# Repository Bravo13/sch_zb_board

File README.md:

# Schneider Sedna Wallswitch ZigBee board
To make regular switch ZigBee-powered and keep it compact

## Hardware
- E18-MS1-PCB(CC2530 board)
- button
- led
- capacitor
- CR2032 battery holder(multicomp bc2001)
- battery

### Additions
Pin length - 18mm

## Software

### Firmware
All firmwares are done with great tool [Configurable ZigBee Firmware](https://github.com/ptvoinfo/zigbee-configurable-firmware)

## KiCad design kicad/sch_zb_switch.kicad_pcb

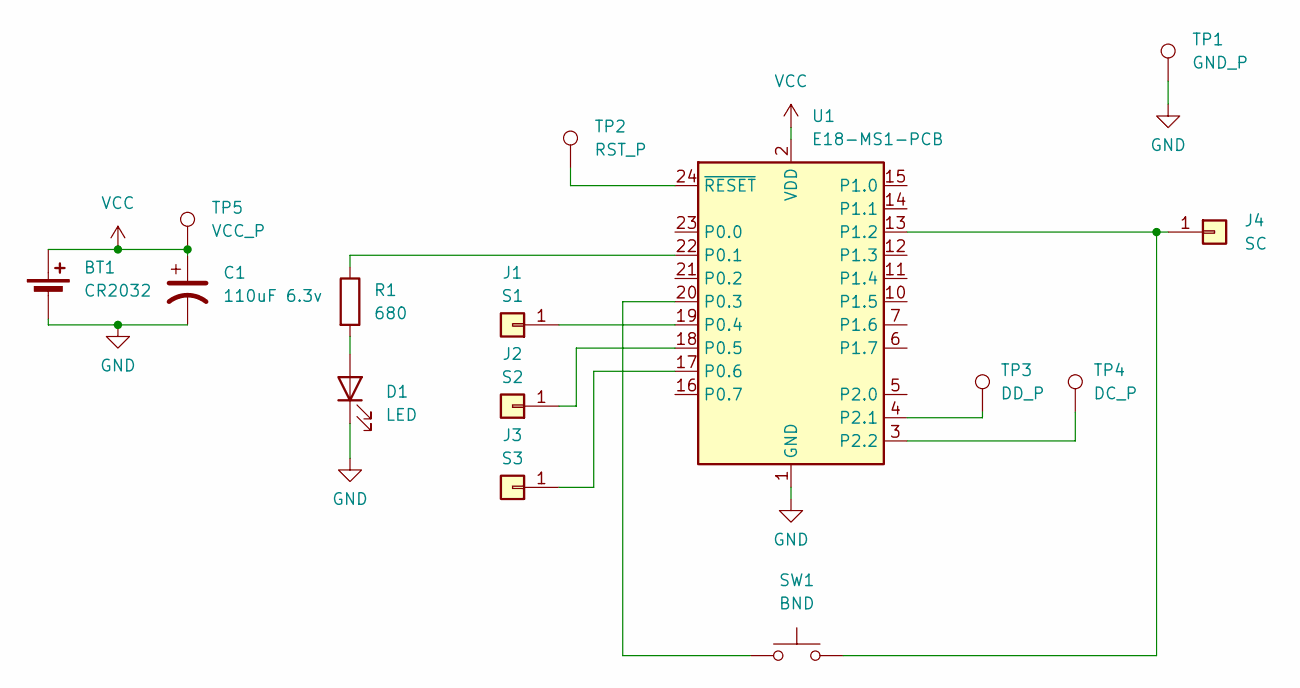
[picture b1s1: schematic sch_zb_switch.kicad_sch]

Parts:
BT1: CR2032; BatteryHolder_Multicomp_BC-2001_1x2032
C1: 110uF 6.3v; CP_EIA-3528-21_Kemet-B_Pad1.50x2.35mm_HandSolder
D1: LED; LED_1206_3216Metric_Pad1.42x1.75mm_HandSolder
J1: S1; SolderWire-1.5sqmm_1x01_D1.7mm_OD3mm
J2: S2; SolderWire-1.5sqmm_1x01_D1.7mm_OD3mm
J3: S3; SolderWire-1.5sqmm_1x01_D1.7mm_OD3mm
J4: SC; SolderWire-1.5sqmm_1x01_D1.7mm_OD3mm
R1: 680; R_1206_3216Metric_Pad1.30x1.75mm_HandSolder
SW1: BND; TS-017a
TP1: GND_P; TestPoint_Pad_D2.0mm
TP2: RST_P; TestPoint_Pad_D2.0mm
TP3: DD_P; TestPoint_Pad_D2.0mm
TP4: DC_P; TestPoint_Pad_D2.0mm
TP5: VCC_P; TestPoint_Pad_D2.0mm
U1: E18-MS1-PCB

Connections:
GND: BT1.2 (-), C1.2, D1.1 (K), TP1.1, U1.1 (GND)
unnamed: D1.2 (A), R1.2
unnamed: J1.1, U1.19 (P0.4)
unnamed: J2.1, U1.18 (P0.5)
unnamed: J3.1, U1.17 (P0.6)
unnamed: J4.1, SW1.1, U1.13 (P1.2)
unnamed: R1.1, U1.22 (P0.1)
unnamed: SW1.2, U1.20 (P0.3)
unnamed: TP3.1, U1.4 (P2.1)
unnamed: TP4.1, U1.3 (P2.2)
unnamed: TP2.1, U1.24 (~RESET)
VCC: BT1.1 (+), C1.1, TP5.1, U1.2 (VDD)

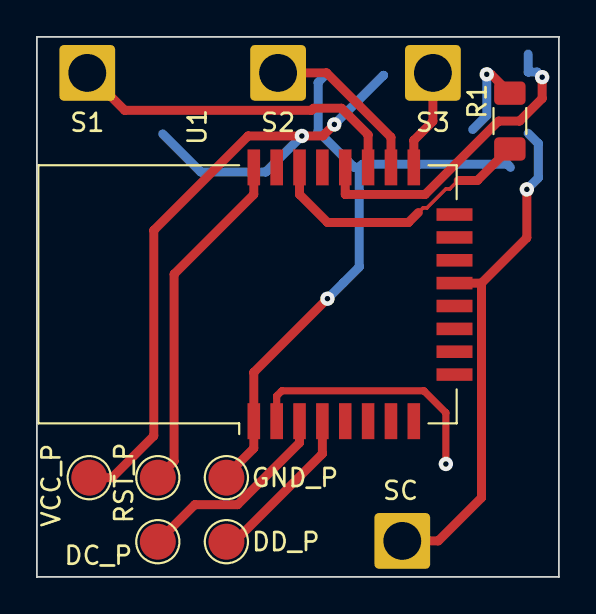
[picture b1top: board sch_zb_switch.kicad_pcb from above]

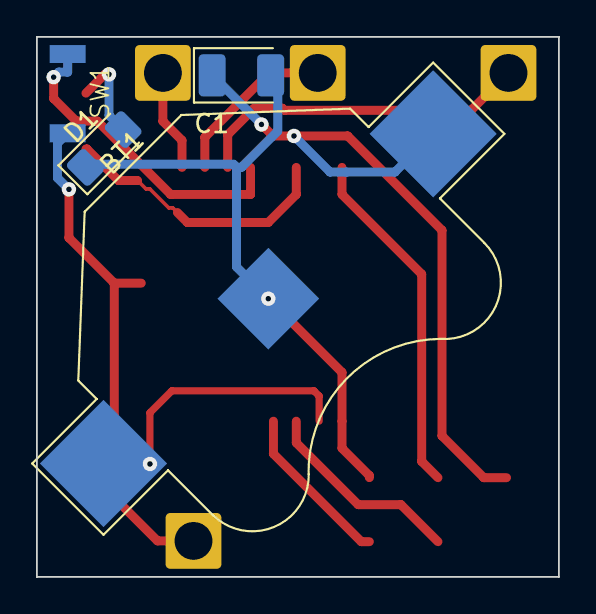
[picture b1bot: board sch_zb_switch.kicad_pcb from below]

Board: 2 copper layers, 29.0 x 30.0 mm, 15 parts (4 on the bottom side), 12 nets.

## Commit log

2024-07-12 init
